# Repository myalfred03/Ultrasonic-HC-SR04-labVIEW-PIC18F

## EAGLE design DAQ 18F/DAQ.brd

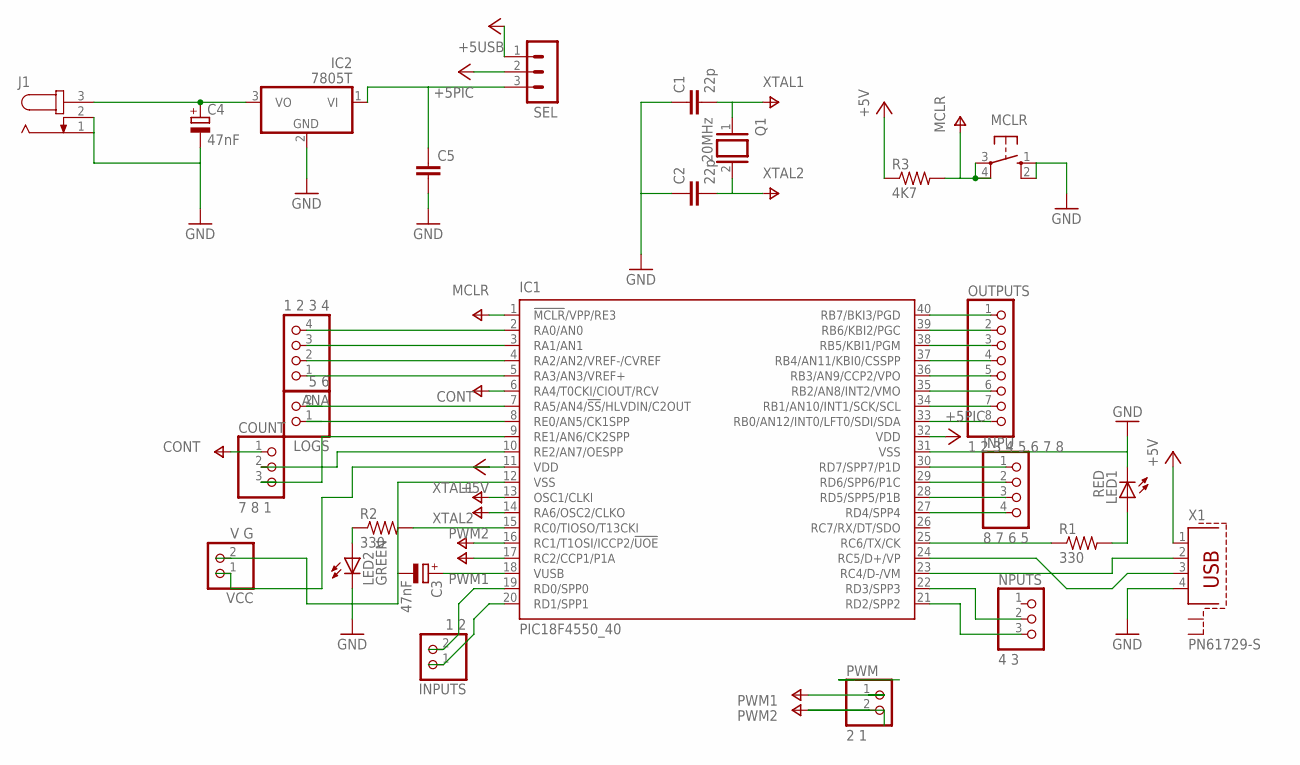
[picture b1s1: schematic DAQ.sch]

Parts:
ANA: 1 2 3 4; 1X04
C1, C2: 22p; C025-024X044
C3, C4: 47nF; E2,5-6E
C5: C-EU050-035X075; C050-035X075
COUNT: 7 8 1; 1X03
IC1: PIC18F4550_40; DIL40
IC2: 7805T; TO220H
INPU: 8 7 6 5; 1X04
INPUTS: 1 2; 1X02
J1: JACK-PLUG0; SPC4077
LED1: RED; LED3MM
LED2: GREEN; LED3MM
LOGS: 5 6; 1X02
MCLR: 10-XX; B3F-10XX
NPUTS: 4 3; 1X03
OUTPUTS: 1 2 3 4 5 6 7 8; 1X08
PWM: 2 1; 1X02
Q1: 20MHz; QS
R1, R2: 330; 0207/10
R3: 4K7; 0207/10
SEL: MA03-1
VCC: V G; 1X02
X1: PN61729-S

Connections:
+5PIC: IC1.11 (VDD), IC1.32 (VDD), R3.1, SEL.2, VCC.1
+5USB: SEL.1, X1.1
CONT: COUNT.1, IC1.6 (RA4/T0CKI/CIOUT/RCV)
GND: C1.1, C2.1, C3.-, C4.-, C5.2, IC1.12 (VSS), IC1.31 (VSS), IC2.2 (GND), J1.1, J1.2, LED1.K (C), LED2.K (C), MCLR.1 (S), MCLR.2 (S1), VCC.2, X1.4
MCLR: IC1.1 (!MCLR!/VPP/RE3), MCLR.3, MCLR.4 (P1), R3.2
unnamed: IC1.23 (RC4/D-/VM), X1.2
unnamed: IC1.30 (RD7/SPP7/P1D), INPU.1
unnamed: IC1.40 (RB7/BKI3/PGD), OUTPUTS.1
unnamed: IC1.15 (RC0/TIOSO/T13CKI), R2.2
unnamed: LED2.A, R2.1
unnamed: IC1.25 (RC6/TX/CK), R1.1
unnamed: LED1.A, R1.2
unnamed: IC1.39 (RB6/KBI2/PGC), OUTPUTS.2
unnamed: IC1.38 (RB5/KBI1/PGM), OUTPUTS.3
unnamed: IC1.37 (RB4/AN11/KBI0/CSSPP), OUTPUTS.4
unnamed: IC1.36 (RB3/AN9/CCP2/VPO), OUTPUTS.5
unnamed: IC1.35 (RB2/AN8/INT2/VMO), OUTPUTS.6
unnamed: IC1.34 (RB1/AN10/INT1/SCK/SCL), OUTPUTS.7
unnamed: IC1.33 (RB0/AN12/INT0/LFT0/SDI/SDA), OUTPUTS.8
unnamed: IC1.24 (RC5/D+/VP), X1.3
unnamed: IC1.29 (RD6/SPP6/P1C), INPU.2
unnamed: IC1.28 (RD5/SPP5/P1B), INPU.3
unnamed: IC1.27 (RD4/SPP4), INPU.4
unnamed: IC1.19 (RD0/SPP0), INPUTS.2
unnamed: C3.+, IC1.18 (VUSB)
unnamed: IC1.21 (RD2/SPP2), NPUTS.3
unnamed: IC1.22 (RD3/SPP3), NPUTS.2
unnamed: ANA.4, IC1.2 (RA0/AN0)
unnamed: ANA.3, IC1.3 (RA1/AN1)
unnamed: ANA.2, IC1.4 (RA2/AN2/VREF-/CVREF)
unnamed: ANA.1, IC1.5 (RA3/AN3/VREF+)
unnamed: IC1.7 (RA5/AN4/!SS!/HLVDIN/C2OUT), LOGS.2
unnamed: IC1.8 (RE0/AN5/CK1SPP), LOGS.1
unnamed: IC1.20 (RD1/SPP1), INPUTS.1
unnamed: COUNT.3, IC1.9 (RE1/AN6/CK2SPP)
unnamed: COUNT.2, IC1.10 (RE2/AN7/OESPP)
unnamed: C4.+, IC2.3 (VO), J1.3
unnamed: C5.1, IC2.1 (VI), SEL.3
PWM1: IC1.17 (RC2/CCP1/P1A), PWM.1
PWM2: IC1.16 (RC1/T1OSI/ICCP2/!UOE), PWM.2
XTAL1: C1.2, IC1.13 (OSC1/CLKI), Q1.1
XTAL2: C2.2, IC1.14 (RA6/OSC2/CLKO), Q1.2

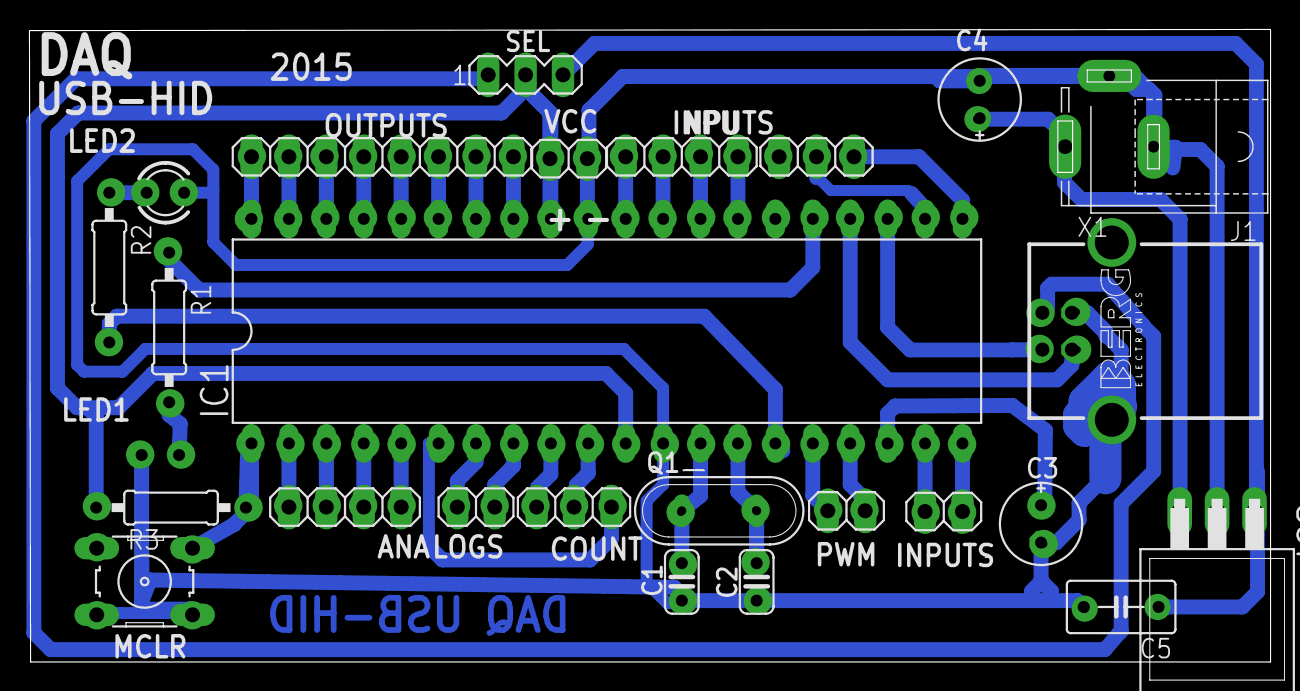
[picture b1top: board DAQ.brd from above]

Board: 2 copper layers, 84.2 x 42.9 mm, 26 parts (1 on the bottom side), 42 nets.

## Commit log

2017-06-19 C & Labview
2017-06-19 Driver USBPC
2017-06-19 PCB board USB Using cadsoft Eagle
2019-01-12 [ImgBot] Optimize images
    *Total -- 336.40kb -> 255.43kb (24.07%)
    /DAQ 18F/eagleUp/eagleUp_DAQ_outline.png -- 7.49kb -> 3.13kb (58.19%)
    /DAQ 18F/eagleUp/eagleUp_DAQ_board_bottom.png -- 65.05kb -> 42.67kb (34.4%)
    /DAQ 18F/eagleUp1/eagleUp_DAQ_board_bottom.png -- 65.05kb -> 42.67kb (34.4%)
    /DAQ 18F/eagleUp/eagleUp_DAQ_bottom_silk.png -- 5.38kb -> 3.88kb (27.87%)
    /DAQ 18F/eagleUp/eagleUp_DAQ_imagesize.png -- 4.12kb -> 3.12kb (24.22%)
